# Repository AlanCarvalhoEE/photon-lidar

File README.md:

# Photon LiDAR
The Photon LiDAR is a small and low-cost 2D LiDAR system based on a ToF laser ranging sensor module.
The project is under development and the first version should be manufactured soon.

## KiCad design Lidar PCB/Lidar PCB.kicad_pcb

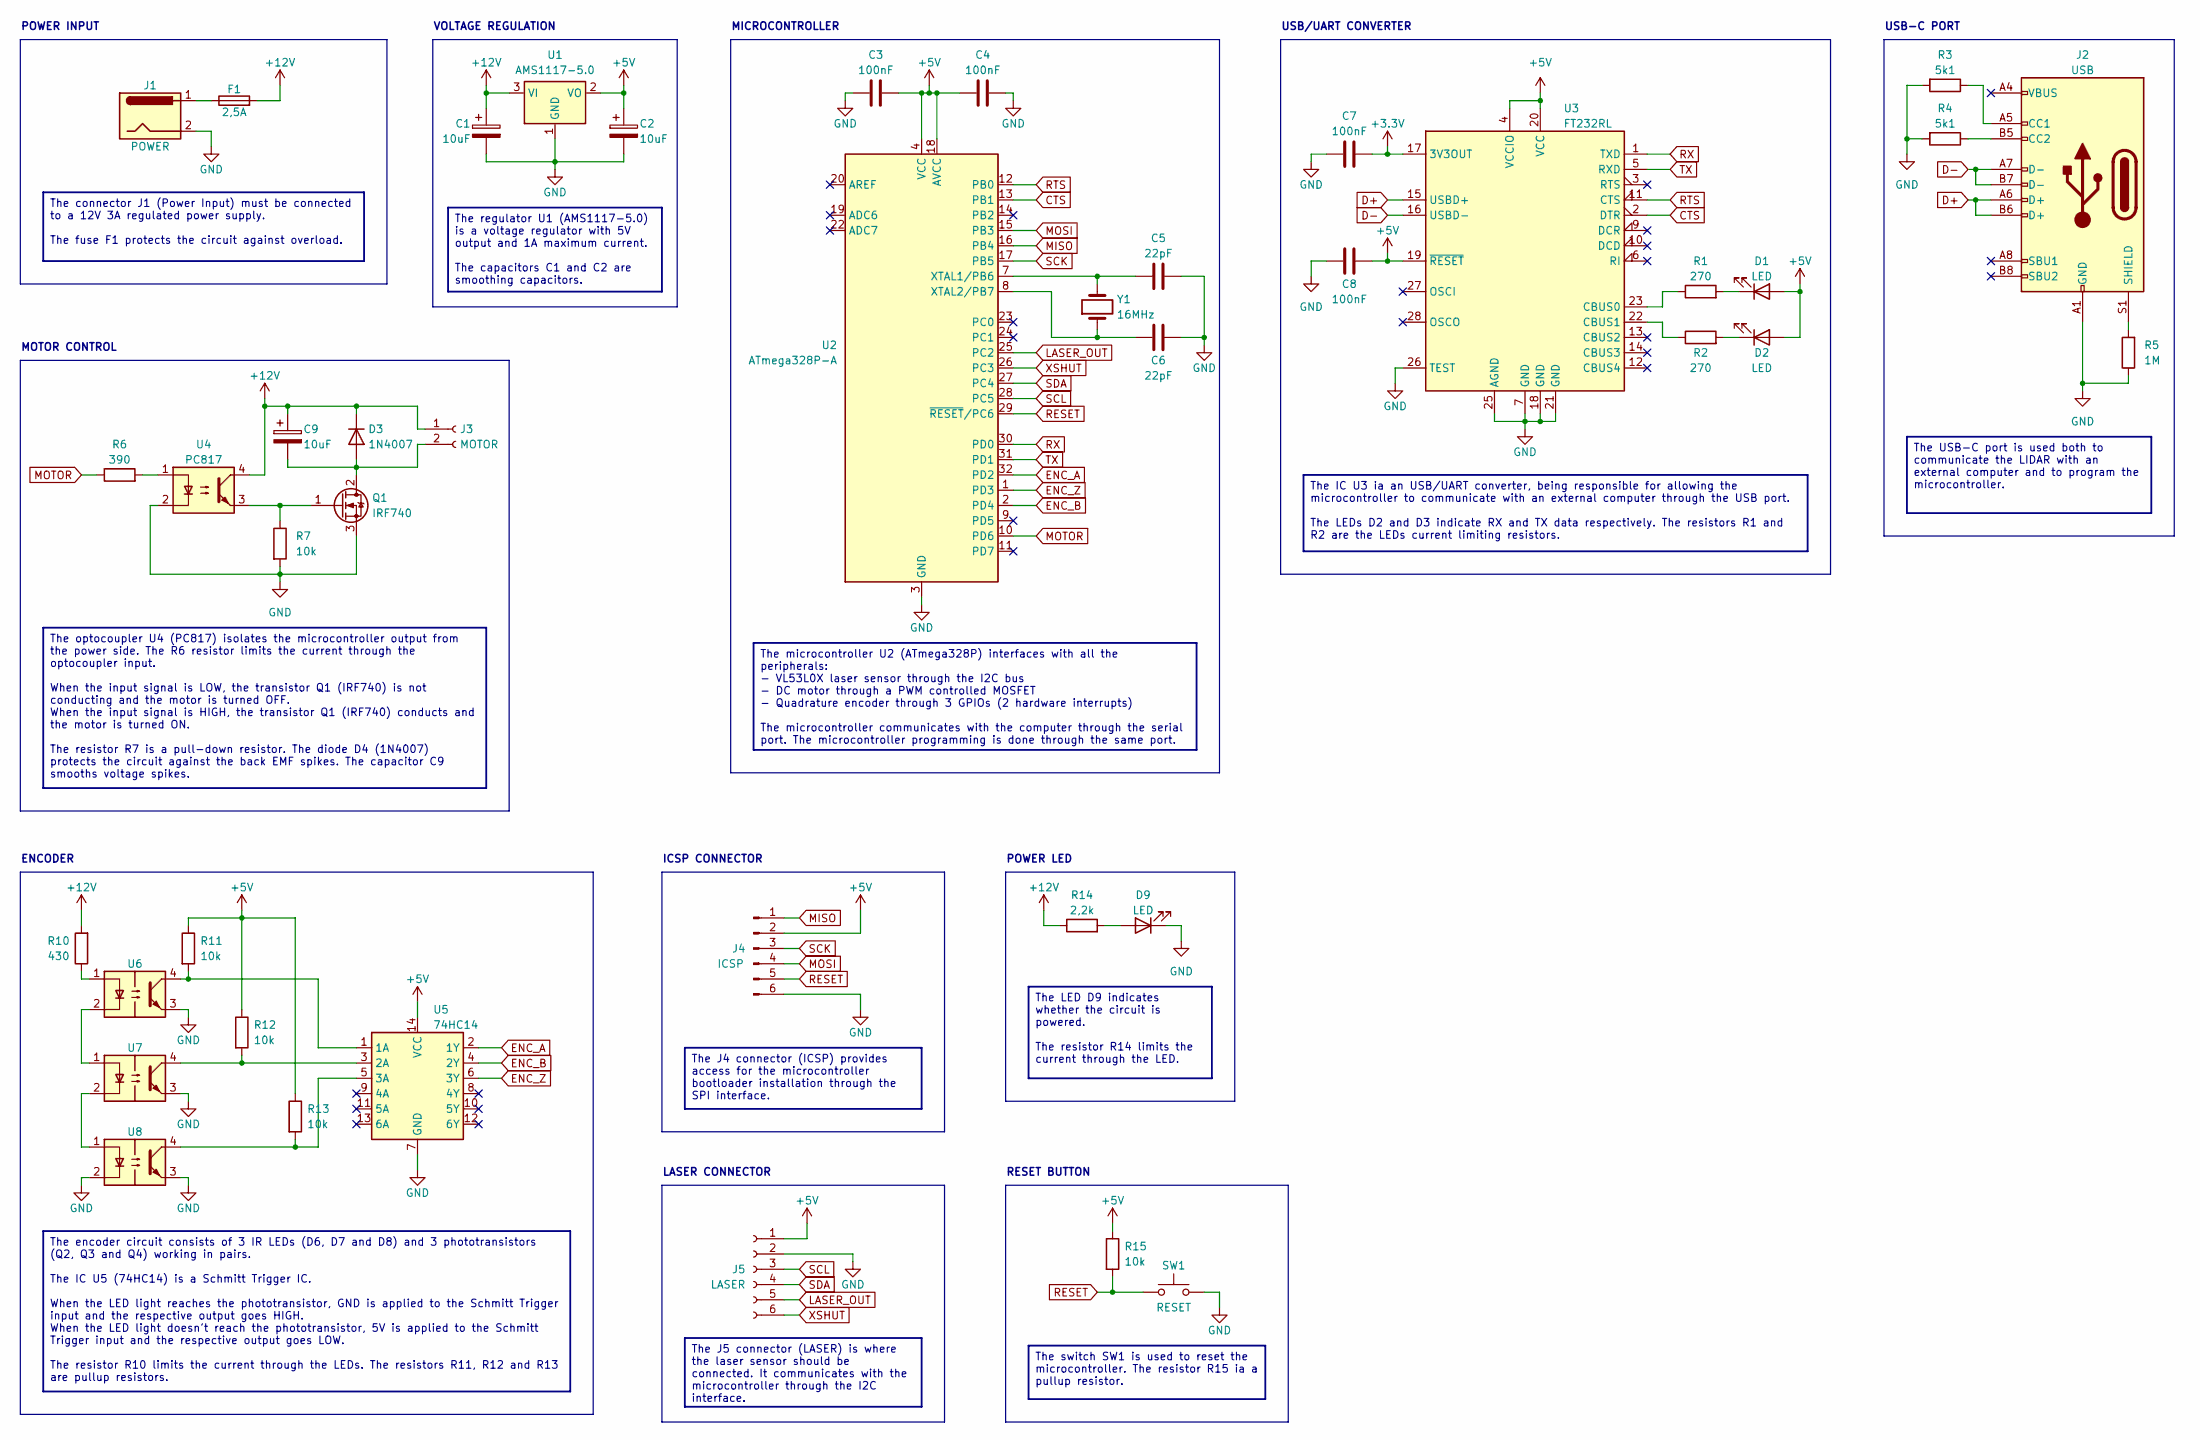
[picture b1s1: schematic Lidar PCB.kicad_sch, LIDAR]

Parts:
C1, C2: 10uF; C_0805_2012Metric; Voltage 16V
C3, C4, C7, C8: 100nF; C_0603_1608Metric; Voltage 10V
C5, C6: 22pF; C_0603_1608Metric; Voltage 16V
C9: 10uF; CP_Elec_4x5.4; Voltage 35V
D1, D2: LED; LED_0603_1608Metric
D3: 1N4007; D_SMA
D9: LED; LED_D3.0mm_Horizontal_O1.27mm_Z10.0mm
F1: 2,5A; Fuse_1206_3216Metric
J1: Barrel_Jack; BarrelJack_GCT_DCJ200-10-A_Horizontal
J2: USB_C_Receptacle_USB2.0; USB_C_Receptacle_Palconn_UTC16-G
J3: Conn_01x02_Socket; JST_XH_B2B-XH-A_1x02_P2.50mm_Vertical
J4: Conn_01x06_Pin; PinSocket_2x03_P2.54mm_Vertical
J5: Conn_01x06_Socket; JST_XH_B6B-XH-A_1x06_P2.50mm_Vertical
Q1: IRF740; TO-220-3_Horizontal_TabDown
R1, R2: 270; R_0603_1608Metric; Tolerance 5%
R3, R4: 5k1; R_0603_1608Metric; Tolerance 1%
R5: 1M; R_0603_1608Metric; Tolerance 5%
R6: 390; R_0603_1608Metric; Tolerance 5%
R7, R11, R12, R13, R15: 10k; R_0603_1608Metric; Tolerance 5%
R10: 430; R_0603_1608Metric; Tolerance 5%
R14: 2,2k; R_0603_1608Metric; Tolerance 5%
SW1: SW_Push; SW_Tactile_SPST_Angled_PTS645Vx39-2LFS
U1: AMS1117-5.0; SOT-223-3_TabPin2
U2: ATmega328P-A; TQFP-32_7x7mm_P0.8mm
U3: FT232RL; SSOP-28_5.3x10.2mm_P0.65mm
U4: PC817; DIP-4_W7.62mm
U5: 74HC14; SOIC-14_3.9x8.7mm_P1.27mm
U6, U7, U8: Optical_Switch
Y1: 16MHz; Crystal_SMD_HC49-SD

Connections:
+3.3V: C7.2, U3.17 (3V3OUT)
+5V: C2.1, C3.2, C4.2, C8.2, D1.2 (A), D2.2 (A), J4.2, J5.1, R11.1, R12.1, R13.1, R15.1, U1.2 (VO), U2.4 (VCC), U2.6 (VCC), U2.18 (AVCC), U3.4 (VCCIO), U3.19 (~RESET), U3.20 (VCC), U5.14 (VCC)
+12V: C1.1, C9.1, D3.1 (K), F1.2, J3.1, R10.2, R14.1, U1.3 (VI), U4.4
CTS: U2.13 (PB1), U3.2 (DTR)
D+: J2.A6 (D+), J2.B6 (D+), U3.15 (USBD+)
D-: J2.A7 (D-), J2.B7 (D-), U3.16 (USBD-)
ENC_A: U2.32 (PD2), U5.2 (1Y)
ENC_B: U2.2 (PD4), U5.4 (2Y)
ENC_Z: U2.1 (PD3), U5.6 (3Y)
GND: C1.2, C2.2, C3.1, C4.1, C5.2, C6.2, C7.1, C8.1, D9.1 (K), J1.2, J2.A1 (GND), J2.A12 (GND), J2.B1 (GND), J2.B12 (GND), J4.6, J5.2, Q1.3 (S), R3.2, R4.2, R5.1, R7.2, SW1.2, U1.1 (GND), U2.3 (GND), U2.5 (GND), U2.21 (GND), U3.7 (GND), U3.18 (GND), U3.21 (GND), U3.25 (AGND), U3.26 (TEST), U4.2, U5.7 (GND), U6.3, U7.3, U8.2, U8.3
LASER_OUT: J5.5, U2.25 (PC2)
MISO: J4.1, U2.16 (PB4)
MOSI: J4.4, U2.15 (PB3)
MOTOR: R6.1, U2.10 (PD6)
unnamed: D1.1 (K), R1.2
unnamed: D2.1 (K), R2.2
unnamed: C9.2, D3.2 (A), J3.2, Q1.2 (D)
unnamed: D9.2 (A), R14.2
unnamed: F1.1, J1.1
unnamed: J2.A5 (CC1), R3.1
unnamed: J2.B5 (CC2), R4.1
unnamed: J2.S1 (SHIELD), R5.2
unnamed: Q1.1 (G), R7.1, U4.3
unnamed: R6.2, U4.1
unnamed: R10.1, U6.1
unnamed: C5.1, U2.7 (XTAL1/PB6), Y1.2
unnamed: C6.1, U2.8 (XTAL2/PB7), Y1.1
unnamed: R1.1, U3.23 (CBUS0)
unnamed: R2.1, U3.22 (CBUS1)
unnamed: R11.2, U5.1 (1A), U6.4
unnamed: R12.2, U5.3 (2A), U7.4
unnamed: R13.2, U5.5 (3A), U8.4
unnamed: U6.2, U7.1
unnamed: U7.2, U8.1
RESET: J4.5, R15.2, SW1.1, U2.29 (~RESET/PC6)
RTS: U2.12 (PB0), U3.11 (CTS)
RX: U2.30 (PD0), U3.1 (TXD)
SCK: J4.3, U2.17 (PB5)
SCL: J5.3, U2.28 (PC5)
SDA: J5.4, U2.27 (PC4)
TX: U2.31 (PD1), U3.5 (RXD)
XSHUT: J5.6, U2.26 (PC3)

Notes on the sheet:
The IC U3 ia an USB/UART converter, being responsible for allowing the microcontroller to communicate with an external computer through the USB port. The LEDs D2 and D3 indicate RX and TX data respectively. The resistors R1 and R2 are the LEDs current limiting resistors.
The connector J1 (Power Input) must be connected to a 12V 3A regulated power supply. The fuse F1 protects the circuit against overload.
The J5 connector (LASER) is where the laser sensor should be connected. It communicates with the microcontroller through the I2C interface.
The microcontroller U2 (ATmega328P) interfaces with all the peripherals: - VL53L0X laser sensor through the I2C bus - DC motor through a PWM controlled MOSFET - Quadrature encoder through 3 GPIOs (2 hardware interrupts) The microcontroller communicates with the computer through the serial port. The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
The LED D9 indicates whether the circuit is powered. The resistor R14 limits the current through the LED.
The USB-C port is used both to communicate the LIDAR with an external computer and to program the microcontroller.
The regulator U1 (AMS1117-5.0) is a voltage regulator with 5V output and 1A maximum current. The capacitors C1 and C2 are smoothing capacitors.
The switch SW1 is used to reset the microcontroller. The resistor R15 ia a pullup resistor.
The optocoupler U4 (PC817) isolates the microcontroller output from the power side. The R6 resistor limits the current through the optocoupler input. When the input signal is LOW, the transistor Q1 (IRF740) is not conducting and the motor is turned OFF. When the input signal is HIGH, the transistor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
The encoder circuit consists of 3 IR LEDs (D6, D7 and D8) and 3 phototransistors (Q2, Q3 and Q4) working in pairs. The IC U5 (74HC14) is a Schmitt Trigger IC. When the LED light reaches the phototransistor, GND is applied to the Schmitt Trigger input and the respective output goes HIGH. When the LE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
The J4 connector (ICSP) provides access for the microcontroller bootloader installation through the SPI interface.
LASER CONNECTOR
USB/UART CONVERTER
RESET BUTTON
MOTOR CONTROL
ENCODER
USB-C PORT
POWER LED
POWER INPUT
VOLTAGE REGULATION
ICSP CONNECTOR
MICROCONTROLLER

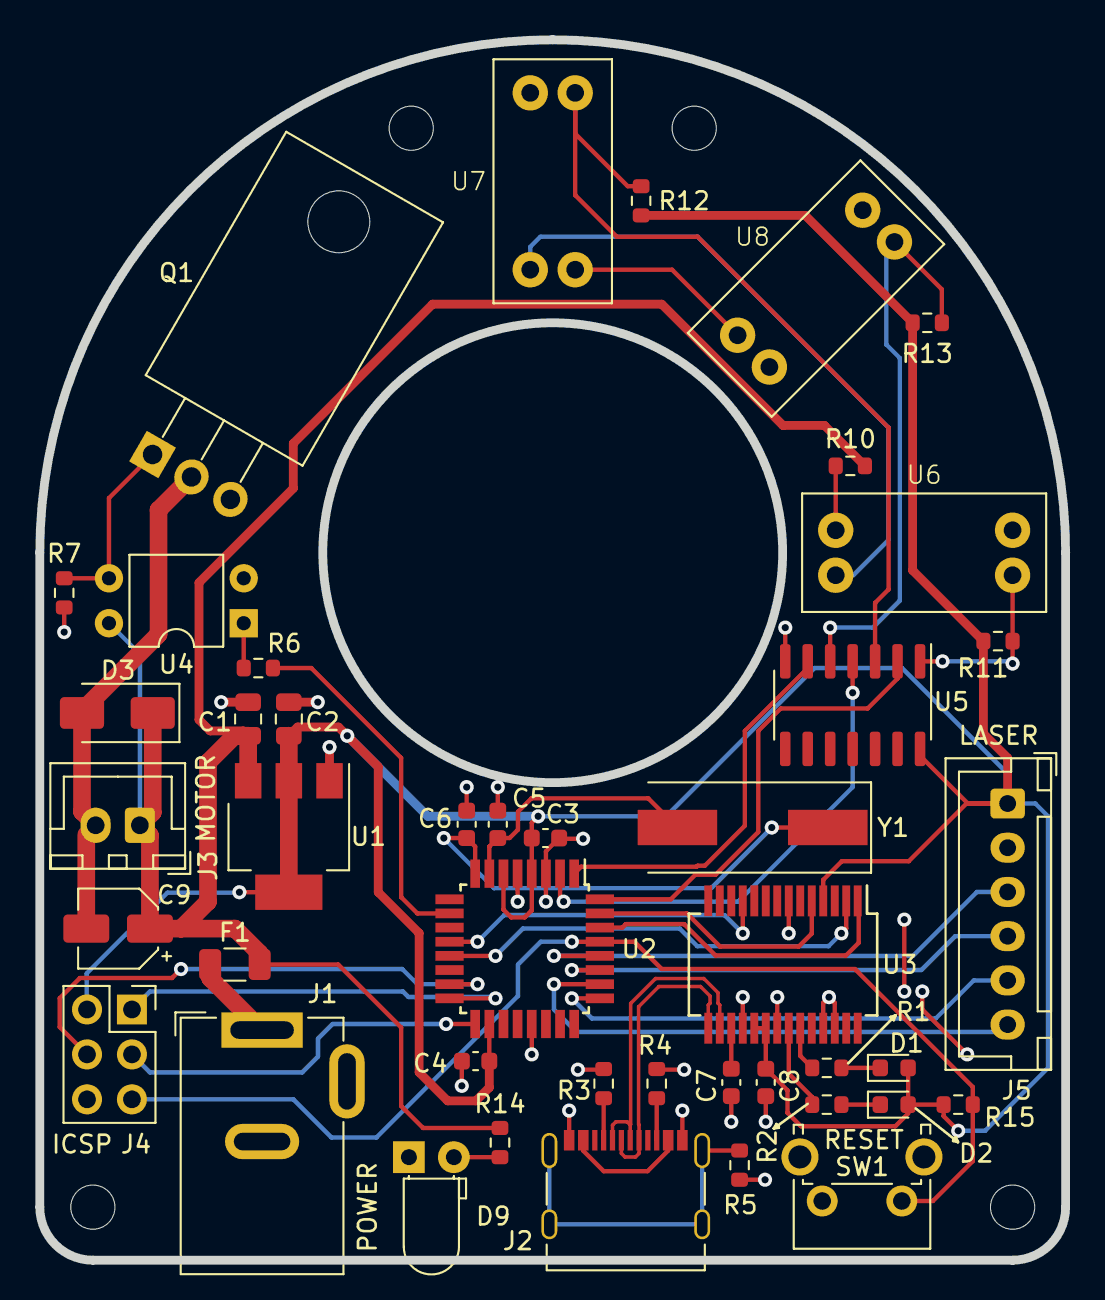
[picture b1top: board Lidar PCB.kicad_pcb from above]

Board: 2 copper layers, 58.0 x 69.0 mm, 43 parts (0 on the bottom side), 42 nets.

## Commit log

2024-01-26 PCB project V1.0 done
2024-02-03 README file included
2024-02-12 First vertion 3D modeling done
2024-02-12 Included information silkscreen on PCB
2024-02-21 PCB input diode removed
2024-02-21 Images included
2024-02-21 gerber files generated
